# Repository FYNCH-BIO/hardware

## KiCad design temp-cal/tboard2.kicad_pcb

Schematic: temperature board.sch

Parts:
C1, C3, C4: C; C_Radial_D4.0mm_H5.0mm_P1.50mm
C2: 1uF; C_Radial_D4.0mm_H5.0mm_P1.50mm
J1: Barrel_Jack; barreljack
J2, J3, J4, J5, J6, J7, J8, J9, J12, J13, J14, J15, J16, J17, J18, J19: Conn_01x02; JSTHeader
J10: Connector_Generic_Conn_02x25_Row_Letter_Last; ADCBoard
J11: Conn_01x04; ethernet cable jack
J20: Conn_02x12_Counter_Clockwise; arduinoChip
J21: Conn_02x09_Odd_Even; RS485
J22: DualDSub; dualDSub9Connector
U1, U2: 9_R_01x10; resistorPackx10

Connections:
+3V3: C3.1, C4.1, J10.45, U1.1, U2.1
+5V: C1.2, J1.1, J10.48, J10.49, J20.24, J21.15
/RJ11_A: J11.2, J21.16, J22.4, J22.13
/RJ11_B: J11.4, J21.18, J22.3, J22.12
/arduA0: J10.46, J20.17
/arduA1: J20.18
/arduA2: J20.19
/arduA3: J20.20
/arduD7: J10.20, J20.10
/arduD8: J10.21, J20.11
/arduD9: J10.22, J20.12
/arduD10: J10.23, J20.13
/arduD11: J10.24, J20.14
/arduD12: J20.15, J21.7
/arduD13: J20.16
/arduRX: J20.2, J21.5
/arduReset: C2.1, J20.3
/arduTX: J20.1, J21.3
/res1: J10.27, J12.1, U2.2
/res2: J10.29, J13.1, U2.3
/res3: J10.31, J14.1, U2.4
/res4: J10.33, J15.1, U2.5
/res5: J10.36, J16.1, U2.6
/res6: J10.38, J17.1, U2.7
/res7: J10.40, J18.1, U2.8
/res8: J10.42, J19.1, U2.9
/res9: J2.1, J10.2, U1.2
/res10: J3.1, J10.4, U1.3
/res11: J4.1, J10.6, U1.4
/res12: J5.1, J10.8, U1.5
/res13: J6.1, J10.11, U1.6
/res14: J7.1, J10.13, U1.7
/res15: J8.1, J10.15, U1.8
/res16: J9.1, J10.17, U1.9
GND: C1.1, C2.2, C3.2, C4.2, J1.2, J2.2, J3.2, J4.2, J5.2, J6.2, J7.2, J8.2, J9.2, J10.1, J10.3, J10.5, J10.7, J10.9, J10.10, J10.12, J10.14, J10.16, J10.18, J10.19, J10.25, J10.26, J10.28, J10.30, J10.32, J10.34, J10.35, J10.37, J10.39, J10.41, J10.43, J10.44, J10.50, J12.2, J13.2, J14.2, J15.2, J16.2, J17.2, J18.2, J19.2, J20.4, J20.23, J21.1, J21.2, J21.17, J22.1, J22.10

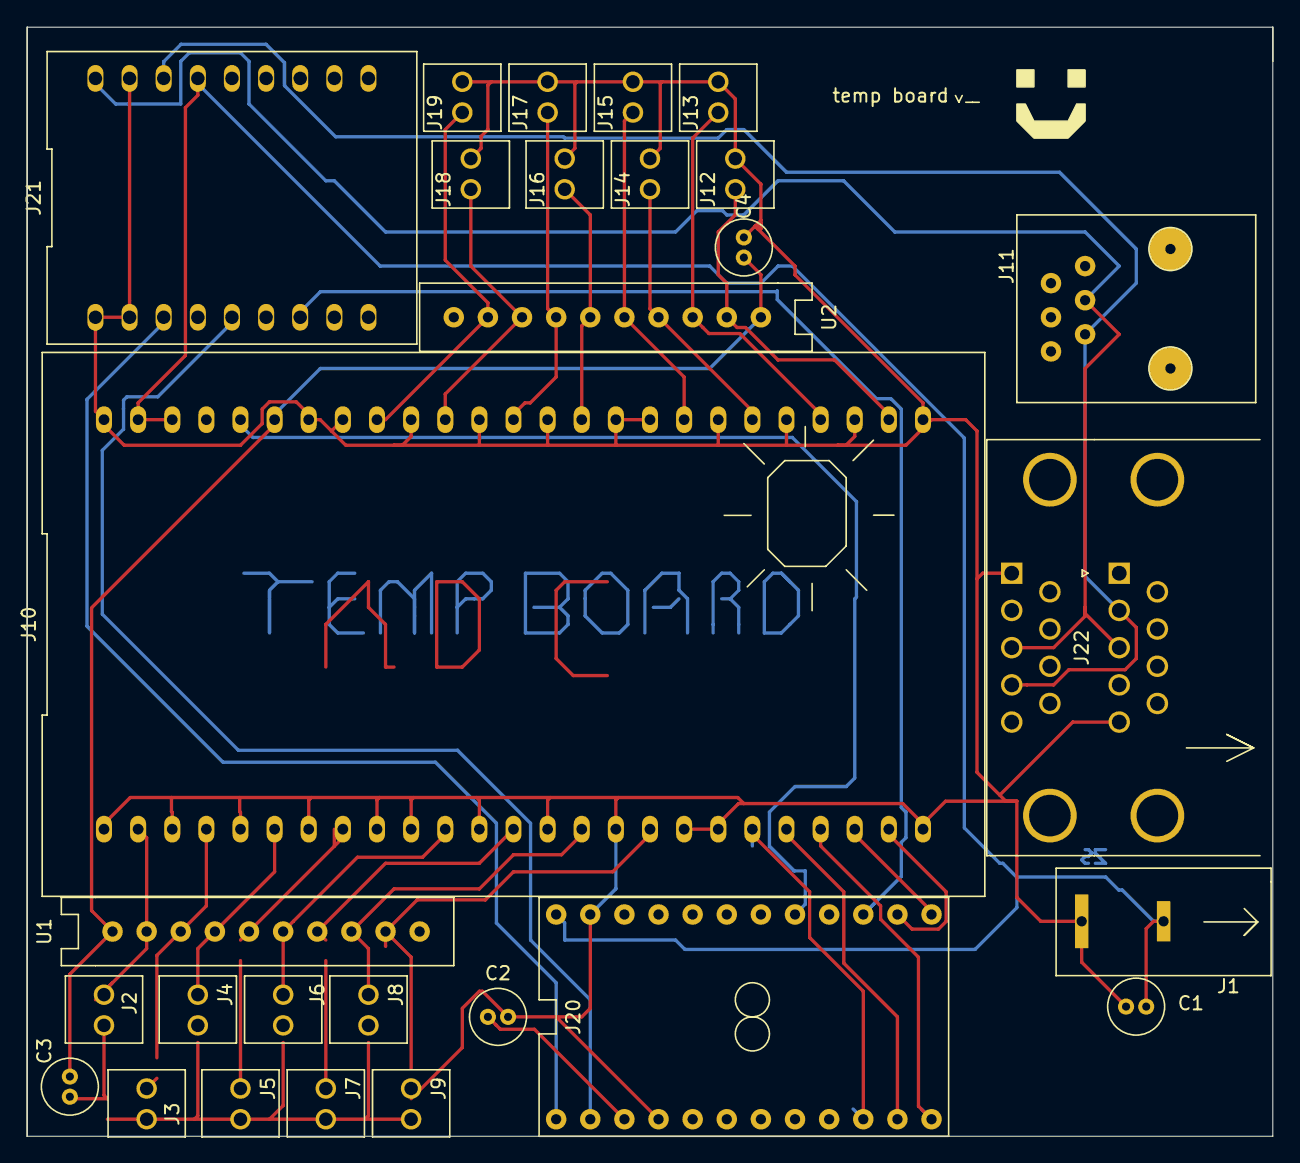
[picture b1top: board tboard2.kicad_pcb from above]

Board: 2 copper layers, 92.7 x 82.5 mm, 28 parts (0 on the bottom side), 31 nets.

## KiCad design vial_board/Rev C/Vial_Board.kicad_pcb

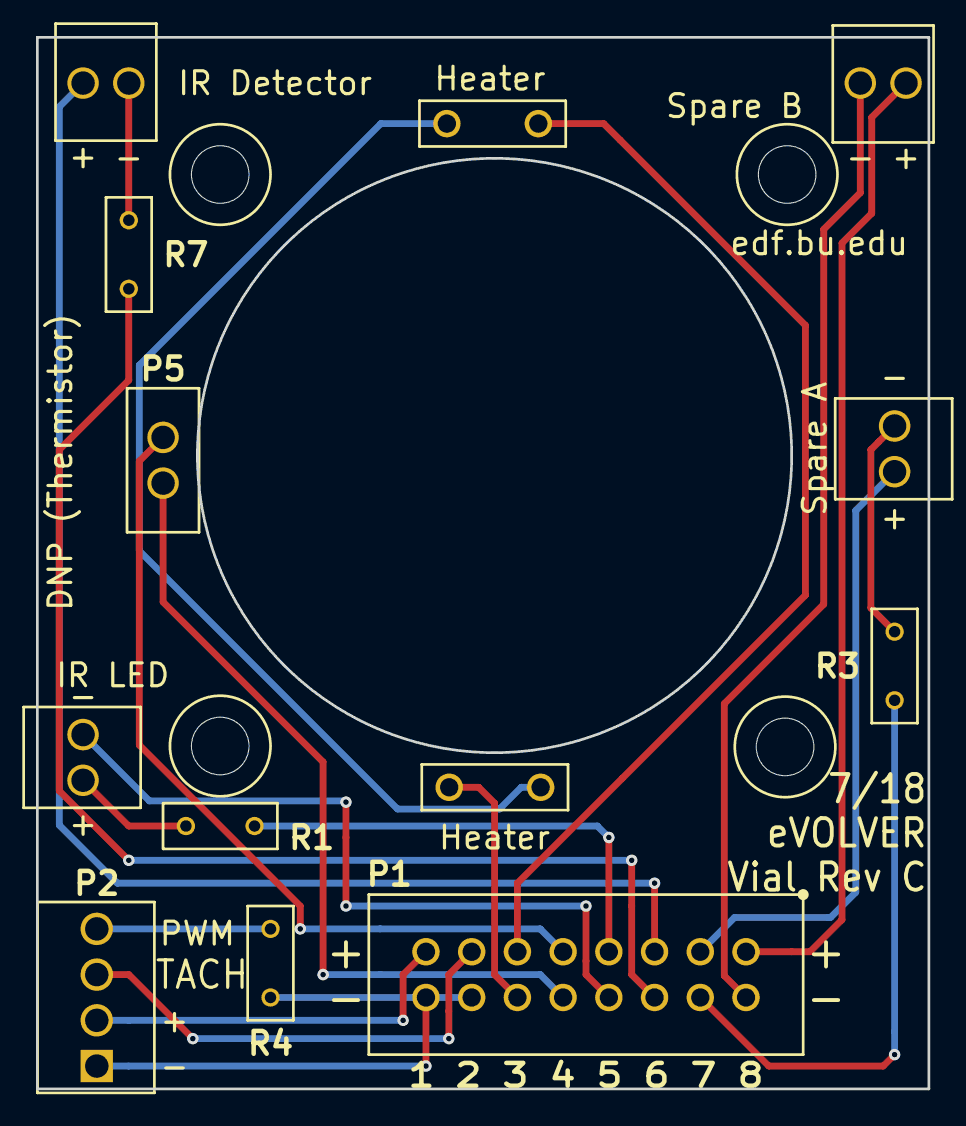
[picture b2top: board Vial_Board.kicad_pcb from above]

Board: 2 copper layers, 49.5 x 58.4 mm, 13 parts (0 on the bottom side), 20 nets.

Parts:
P1: CONN_02X08; 2x8_pin_10in
P2: CONN_01X04; 4_ScrewTerm
P5: DNP (Thermistor); Thermistor
P6: IR LED; screw_terminal
P7: IR Detector; screw_terminal
P8: Spare B; screw_terminal
P9: Spare A; screw_terminal
R1, R3, R7: 82; Through_hole_R
R4: R; Through_hole_R
R5: Heater 1; Heater
R6: Heater 2; Heater

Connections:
/FAN+: P1.15, P2.2
/FAN-: P1.14, P1.16, P2.1, R4.2
/FS+: P1.13, P2.3
/HTR+: P1.11, R5.1
/HTR-: P1.12, R6.2
/LED+: P1.7, R1.1
/LED-: P1.8, P6.2
/PD+: P1.5, P7.1
/PD-: P1.6, R7.2
/PWM: P2.4, R4.1
/SPA+: P1.3, P9.1
/SPA-: P1.4, R3.2
/SPB+: P1.1, P8.1
/SPB-: P1.2, P8.2
/TS+: P1.9, P5.1
/TS-: P1.10, P5.2
unnamed: P6.1, R1.2
unnamed: P7.2, R7.1
unnamed: P9.2, R3.1
unnamed: R5.2, R6.1
